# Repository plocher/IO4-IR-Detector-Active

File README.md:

# IO4-IR-Detector-Active
## License: CERN Open Hardware Licence v1.2

This project started as an AT-Tiny project loosely based on [Paisley\'s designs](http://home.cogeco.ca/~rpaisley4/PhotoDetectors.html) and 
[dustinandrews instructable](http://www.instructables.com/id/Make-an-Attiny13-based-IR-proximity-sensor-for-2/step4/Wire-it-up/).

It evolved from a discrete logic circuit into an AT-Tiny one into a quad detector based on an Arduino core for ease of programming and economy of scale - one '328 is cheaper than 4x tiny's or the original (expensive) remote control TV detectors.  The current version uses a DFRobot to avoid having to low level program the AVR chips with a \'duino bootloader.

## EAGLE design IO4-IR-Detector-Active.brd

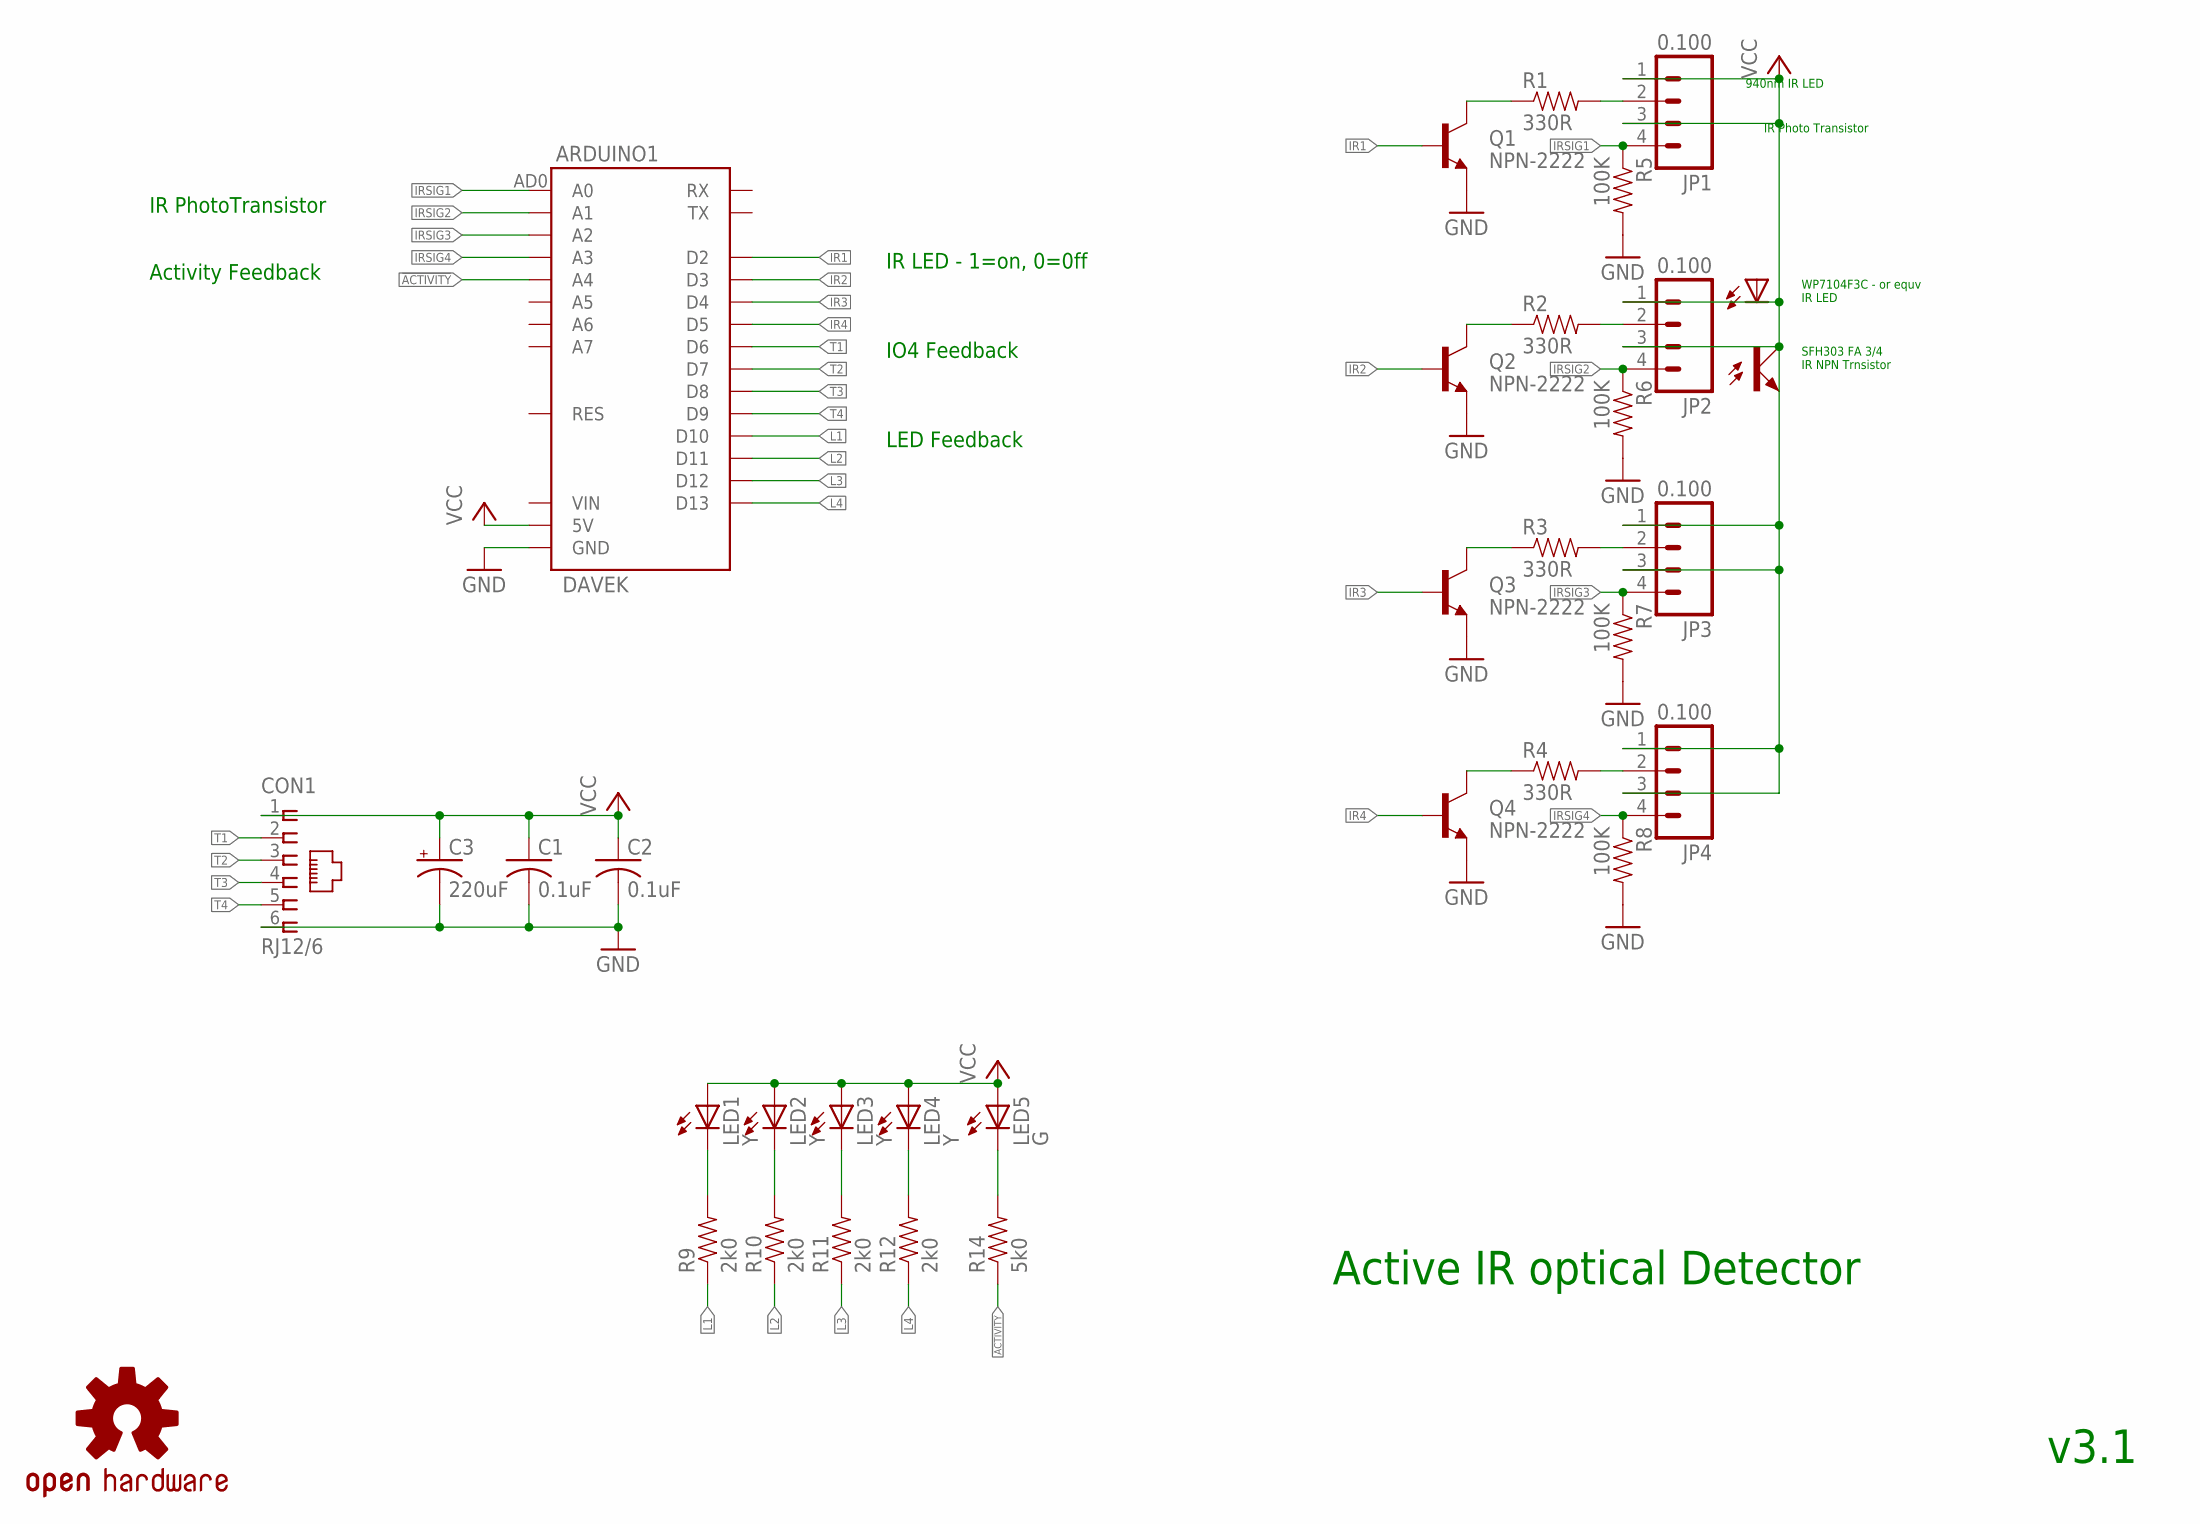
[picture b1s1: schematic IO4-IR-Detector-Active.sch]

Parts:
ARDUINO1: DAVEK; ARDUINO_PRO_MINI_DAVEK
C1, C2: 0.1uF; 0603-CAP
C3: 220uF; 0810-CAP
CON1: RJ12/6; RJ25-PANEL
JP1, JP2, JP3, JP4: 0.100; 1X04_LOCK
LED1, LED2, LED3, LED4: Y; 0603-LED
LED5: G; 0603-LED
OSH_LOGO: DOC-OSHW-LOGO-S; OSHW-LOGO-S
Q1, Q2, Q3, Q4: NPN-2222; SOT23
R1, R2, R3, R4: 330R; 0603-RES
R5, R6, R7, R8: 100K; 0603-RES
R9, R10, R11, R12: 2k0; 0603-RES
R14: 5k0; 0603-RES

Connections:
!ACTIVITY: ARDUINO1.AD4 (A4), R14.1
GND: ARDUINO1.GND@1 (GND), ARDUINO1.GND@2 (GND), ARDUINO1.GND@4 (GND), C1.2, C2.2, C3.-, CON1.6, Q1.2 (E), Q2.2 (E), Q3.2 (E), Q4.2 (E), R5.2, R6.2, R7.2, R8.2
IR1: ARDUINO1.D2, Q1.1 (B)
IR2: ARDUINO1.D3, Q2.1 (B)
IR3: ARDUINO1.D4, Q3.1 (B)
IR4: ARDUINO1.D5, Q4.1 (B)
IRDRIVE1: Q1.3 (C), R1.1
IRDRIVE2: Q2.3 (C), R2.1
IRDRIVE3: Q3.3 (C), R3.1
IRDRIVE4: Q4.3 (C), R4.1
IRSIG1: ARDUINO1.AD0 (A0), JP1.4, R5.1
IRSIG2: ARDUINO1.AD1 (A1), JP2.4, R6.1
IRSIG3: ARDUINO1.AD2 (A2), JP3.4, R7.1
IRSIG4: ARDUINO1.AD3 (A3), JP4.4, R8.1
L1: ARDUINO1.D10, R9.1
L2: ARDUINO1.D11, R10.1
L3: ARDUINO1.D12, R11.1
L4: ARDUINO1.D13, R12.1
unnamed: LED5.C, R14.2
unnamed: JP1.2, R1.2
unnamed: JP2.2, R2.2
unnamed: JP3.2, R3.2
unnamed: JP4.2, R4.2
unnamed: LED1.C, R9.2
unnamed: LED2.C, R10.2
unnamed: LED3.C, R11.2
unnamed: LED4.C, R12.2
T1: ARDUINO1.D6, CON1.2
T2: ARDUINO1.D7, CON1.3
T3: ARDUINO1.D8, CON1.4
T4: ARDUINO1.D9, CON1.5
VCC: ARDUINO1.5V, C1.1, C2.1, C3.+, CON1.1, JP1.1, JP1.3, JP2.1, JP2.3, JP3.1, JP3.3, JP4.1, JP4.3, LED1.A, LED2.A, LED3.A, LED4.A, LED5.A

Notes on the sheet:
Active IR optical Detector
v3.1
940nm IR LED
IR Photo Transistor
WP7104F3C - or equv IR LED
SFH303 FA 3/4 IR NPN Trnsistor
IR LED - 1=on, 0=0ff
IR PhotoTransistor
IO4 Feedback
LED Feedback
Activity Feedback

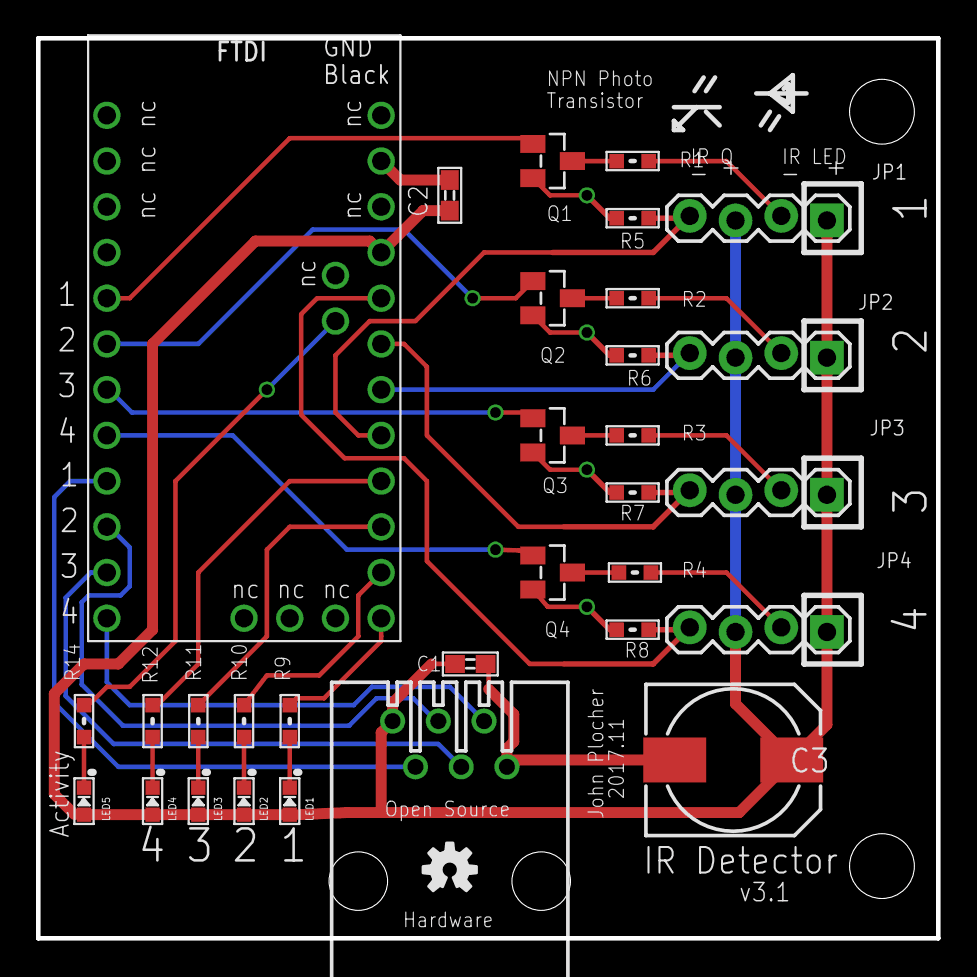
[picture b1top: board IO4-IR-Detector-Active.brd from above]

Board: 2 copper layers, 50.0 x 50.0 mm, 32 parts (0 on the bottom side), 32 nets.

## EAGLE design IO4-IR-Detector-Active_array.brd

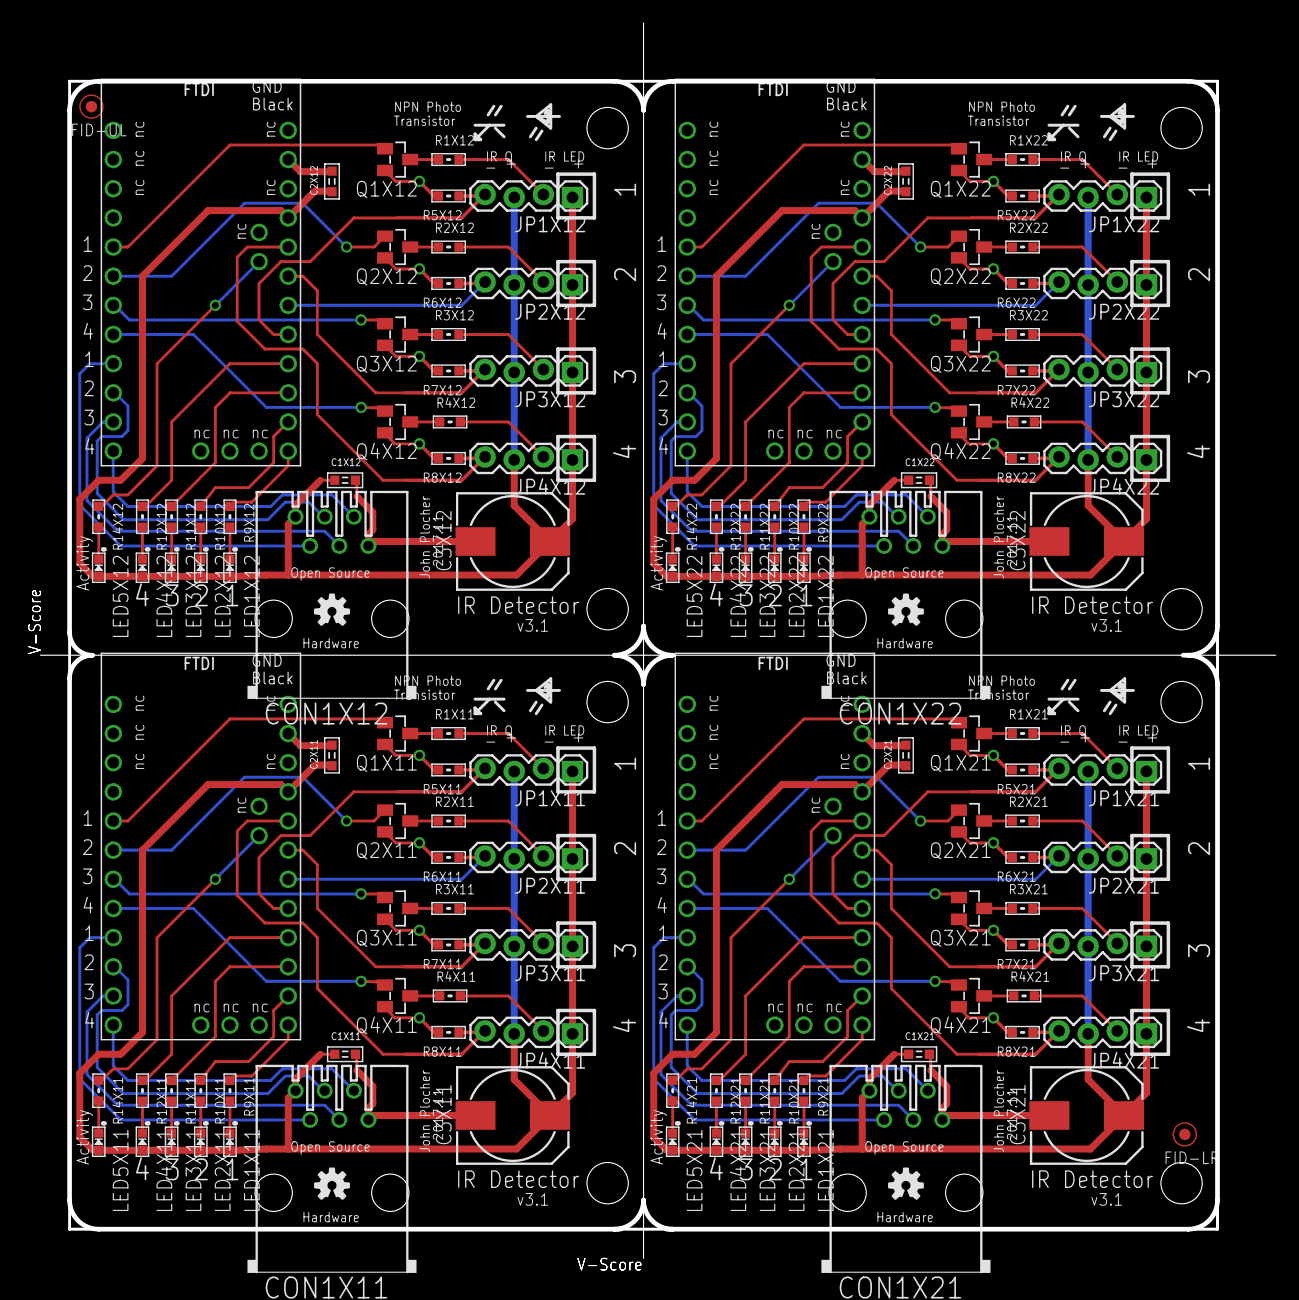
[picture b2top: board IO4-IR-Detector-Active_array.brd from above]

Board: 2 copper layers, 108.7 x 108.8 mm, 130 parts (0 on the bottom side), 128 nets.

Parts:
ARDUINO1X11, ARDUINO1X12, ARDUINO1X21, ARDUINO1X22: DAVEK; ARDUINO_PRO_MINI_DAVEK
C1X11, C1X12, C1X21, C1X22, C2X11, C2X12, C2X21, C2X22: 0.1uF; 0603-CAP
C3X11, C3X12, C3X21, C3X22: 220uF; 0810-CAP
CON1X11, CON1X12, CON1X21, CON1X22: RJ12/6; RJ25-PANEL
FID-LR: FIDUCIAL_1MM
FID-UL: FIDUCIAL_1MM
JP1X11, JP1X12, JP1X21, JP1X22, JP2X11, JP2X12, JP2X21, JP2X22, JP3X11, JP3X12, JP3X21, JP3X22, JP4X11, JP4X12, JP4X21, JP4X22: 0.100; 1X04_LOCK
LED1X11, LED1X12, LED1X21, LED1X22, LED2X11, LED2X12, LED2X21, LED2X22, LED3X11, LED3X12, LED3X21, LED3X22, LED4X11, LED4X12, LED4X21, LED4X22: Y; 0603-LED
LED5X11, LED5X12, LED5X21, LED5X22: G; 0603-LED
OSH_LOGOX11, OSH_LOGOX12, OSH_LOGOX21, OSH_LOGOX22: DOC-OSHW-LOGO-S; OSHW-LOGO-S
Q1X11, Q1X12, Q1X21, Q1X22, Q2X11, Q2X12, Q2X21, Q2X22, Q3X11, Q3X12, Q3X21, Q3X22, Q4X11, Q4X12, Q4X21, Q4X22: NPN-2222; SOT23
R1X11, R1X12, R1X21, R1X22, R2X11, R2X12, R2X21, R2X22, R3X11, R3X12, R3X21, R3X22, R4X11, R4X12, R4X21, R4X22: 330R; 0603-RES
R5X11, R5X12, R5X21, R5X22, R6X11, R6X12, R6X21, R6X22, R7X11, R7X12, R7X21, R7X22, R8X11, R8X12, R8X21, R8X22: 100K; 0603-RES
R9X11, R9X12, R9X21, R9X22, R10X11, R10X12, R10X21, R10X22, R11X11, R11X12, R11X21, R11X22, R12X11, R12X12, R12X21, R12X22: 2k0; 0603-RES
R14X11, R14X12, R14X21, R14X22: 5k0; 0603-RES

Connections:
!ACTIVITYX11: ARDUINO1X11.AD4, R14X11.1
!ACTIVITYX12: ARDUINO1X12.AD4, R14X12.1
!ACTIVITYX21: ARDUINO1X21.AD4, R14X21.1
!ACTIVITYX22: ARDUINO1X22.AD4, R14X22.1
GNDX11: ARDUINO1X11.GND@1, ARDUINO1X11.GND@2, ARDUINO1X11.GND@4, C1X11.2, C2X11.2, C3X11.-, CON1X11.6, Q1X11.2, Q2X11.2, Q3X11.2, Q4X11.2, R5X11.2, R6X11.2, R7X11.2, R8X11.2
GNDX12: ARDUINO1X12.GND@1, ARDUINO1X12.GND@2, ARDUINO1X12.GND@4, C1X12.2, C2X12.2, C3X12.-, CON1X12.6, Q1X12.2, Q2X12.2, Q3X12.2, Q4X12.2, R5X12.2, R6X12.2, R7X12.2, R8X12.2
GNDX21: ARDUINO1X21.GND@1, ARDUINO1X21.GND@2, ARDUINO1X21.GND@4, C1X21.2, C2X21.2, C3X21.-, CON1X21.6, Q1X21.2, Q2X21.2, Q3X21.2, Q4X21.2, R5X21.2, R6X21.2, R7X21.2, R8X21.2
GNDX22: ARDUINO1X22.GND@1, ARDUINO1X22.GND@2, ARDUINO1X22.GND@4, C1X22.2, C2X22.2, C3X22.-, CON1X22.6, Q1X22.2, Q2X22.2, Q3X22.2, Q4X22.2, R5X22.2, R6X22.2, R7X22.2, R8X22.2
IR1X11: ARDUINO1X11.D2, Q1X11.1
IR1X12: ARDUINO1X12.D2, Q1X12.1
IR1X21: ARDUINO1X21.D2, Q1X21.1
IR1X22: ARDUINO1X22.D2, Q1X22.1
IR2X11: ARDUINO1X11.D3, Q2X11.1
IR2X12: ARDUINO1X12.D3, Q2X12.1
IR2X21: ARDUINO1X21.D3, Q2X21.1
IR2X22: ARDUINO1X22.D3, Q2X22.1
IR3X11: ARDUINO1X11.D4, Q3X11.1
IR3X12: ARDUINO1X12.D4, Q3X12.1
IR3X21: ARDUINO1X21.D4, Q3X21.1
IR3X22: ARDUINO1X22.D4, Q3X22.1
IR4X11: ARDUINO1X11.D5, Q4X11.1
IR4X12: ARDUINO1X12.D5, Q4X12.1
IR4X21: ARDUINO1X21.D5, Q4X21.1
IR4X22: ARDUINO1X22.D5, Q4X22.1
IRDRIVE1X11: Q1X11.3, R1X11.1
IRDRIVE1X12: Q1X12.3, R1X12.1
IRDRIVE1X21: Q1X21.3, R1X21.1
IRDRIVE1X22: Q1X22.3, R1X22.1
IRDRIVE2X11: Q2X11.3, R2X11.1
IRDRIVE2X12: Q2X12.3, R2X12.1
IRDRIVE2X21: Q2X21.3, R2X21.1
IRDRIVE2X22: Q2X22.3, R2X22.1
IRDRIVE3X11: Q3X11.3, R3X11.1
IRDRIVE3X12: Q3X12.3, R3X12.1
IRDRIVE3X21: Q3X21.3, R3X21.1
IRDRIVE3X22: Q3X22.3, R3X22.1
IRDRIVE4X11: Q4X11.3, R4X11.1
IRDRIVE4X12: Q4X12.3, R4X12.1
IRDRIVE4X21: Q4X21.3, R4X21.1
IRDRIVE4X22: Q4X22.3, R4X22.1
IRSIG1X11: ARDUINO1X11.AD0, JP1X11.4, R5X11.1
IRSIG1X12: ARDUINO1X12.AD0, JP1X12.4, R5X12.1
IRSIG1X21: ARDUINO1X21.AD0, JP1X21.4, R5X21.1
IRSIG1X22: ARDUINO1X22.AD0, JP1X22.4, R5X22.1
IRSIG2X11: ARDUINO1X11.AD1, JP2X11.4, R6X11.1
IRSIG2X12: ARDUINO1X12.AD1, JP2X12.4, R6X12.1
IRSIG2X21: ARDUINO1X21.AD1, JP2X21.4, R6X21.1
IRSIG2X22: ARDUINO1X22.AD1, JP2X22.4, R6X22.1
IRSIG3X11: ARDUINO1X11.AD2, JP3X11.4, R7X11.1
IRSIG3X12: ARDUINO1X12.AD2, JP3X12.4, R7X12.1
IRSIG3X21: ARDUINO1X21.AD2, JP3X21.4, R7X21.1
IRSIG3X22: ARDUINO1X22.AD2, JP3X22.4, R7X22.1
IRSIG4X11: ARDUINO1X11.AD3, JP4X11.4, R8X11.1
IRSIG4X12: ARDUINO1X12.AD3, JP4X12.4, R8X12.1
IRSIG4X21: ARDUINO1X21.AD3, JP4X21.4, R8X21.1
IRSIG4X22: ARDUINO1X22.AD3, JP4X22.4, R8X22.1
L1X11: ARDUINO1X11.D10, R9X11.1
L1X12: ARDUINO1X12.D10, R9X12.1
L1X21: ARDUINO1X21.D10, R9X21.1
L1X22: ARDUINO1X22.D10, R9X22.1
L2X11: ARDUINO1X11.D11, R10X11.1
L2X12: ARDUINO1X12.D11, R10X12.1
L2X21: ARDUINO1X21.D11, R10X21.1
L2X22: ARDUINO1X22.D11, R10X22.1
L3X11: ARDUINO1X11.D12, R11X11.1
L3X12: ARDUINO1X12.D12, R11X12.1
L3X21: ARDUINO1X21.D12, R11X21.1
L3X22: ARDUINO1X22.D12, R11X22.1
L4X11: ARDUINO1X11.D13, R12X11.1
L4X12: ARDUINO1X12.D13, R12X12.1
L4X21: ARDUINO1X21.D13, R12X21.1
L4X22: ARDUINO1X22.D13, R12X22.1
unnamed: LED5X11.C, R14X11.2
unnamed: LED5X12.C, R14X12.2
unnamed: LED5X21.C, R14X21.2
unnamed: LED5X22.C, R14X22.2
unnamed: JP1X11.2, R1X11.2
unnamed: JP1X12.2, R1X12.2
unnamed: JP1X21.2, R1X21.2
unnamed: JP1X22.2, R1X22.2
unnamed: JP2X11.2, R2X11.2
unnamed: JP2X12.2, R2X12.2
unnamed: JP2X21.2, R2X21.2
unnamed: JP2X22.2, R2X22.2
unnamed: JP3X11.2, R3X11.2
unnamed: JP3X12.2, R3X12.2
unnamed: JP3X21.2, R3X21.2
unnamed: JP3X22.2, R3X22.2
unnamed: JP4X11.2, R4X11.2
unnamed: JP4X12.2, R4X12.2
unnamed: JP4X21.2, R4X21.2
unnamed: JP4X22.2, R4X22.2
unnamed: LED1X11.C, R9X11.2
unnamed: LED1X12.C, R9X12.2
unnamed: LED1X21.C, R9X21.2
unnamed: LED1X22.C, R9X22.2
unnamed: LED2X11.C, R10X11.2
unnamed: LED2X12.C, R10X12.2
unnamed: LED2X21.C, R10X21.2
unnamed: LED2X22.C, R10X22.2
unnamed: LED3X11.C, R11X11.2
unnamed: LED3X12.C, R11X12.2
unnamed: LED3X21.C, R11X21.2
unnamed: LED3X22.C, R11X22.2
unnamed: LED4X11.C, R12X11.2
unnamed: LED4X12.C, R12X12.2
unnamed: LED4X21.C, R12X21.2
unnamed: LED4X22.C, R12X22.2
T1X11: ARDUINO1X11.D6, CON1X11.2
T1X12: ARDUINO1X12.D6, CON1X12.2
T1X21: ARDUINO1X21.D6, CON1X21.2
T1X22: ARDUINO1X22.D6, CON1X22.2
T2X11: ARDUINO1X11.D7, CON1X11.3
T2X12: ARDUINO1X12.D7, CON1X12.3
T2X21: ARDUINO1X21.D7, CON1X21.3
T2X22: ARDUINO1X22.D7, CON1X22.3
T3X11: ARDUINO1X11.D8, CON1X11.4
T3X12: ARDUINO1X12.D8, CON1X12.4
T3X21: ARDUINO1X21.D8, CON1X21.4
T3X22: ARDUINO1X22.D8, CON1X22.4
T4X11: ARDUINO1X11.D9, CON1X11.5
T4X12: ARDUINO1X12.D9, CON1X12.5
T4X21: ARDUINO1X21.D9, CON1X21.5
T4X22: ARDUINO1X22.D9, CON1X22.5
VCCX11: ARDUINO1X11.5V, C1X11.1, C2X11.1, C3X11.+, CON1X11.1, JP1X11.1, JP1X11.3, JP2X11.1, JP2X11.3, JP3X11.1, JP3X11.3, JP4X11.1, JP4X11.3, LED1X11.A, LED2X11.A, LED3X11.A, LED4X11.A, LED5X11.A
VCCX12: ARDUINO1X12.5V, C1X12.1, C2X12.1, C3X12.+, CON1X12.1, JP1X12.1, JP1X12.3, JP2X12.1, JP2X12.3, JP3X12.1, JP3X12.3, JP4X12.1, JP4X12.3, LED1X12.A, LED2X12.A, LED3X12.A, LED4X12.A, LED5X12.A
VCCX21: ARDUINO1X21.5V, C1X21.1, C2X21.1, C3X21.+, CON1X21.1, JP1X21.1, JP1X21.3, JP2X21.1, JP2X21.3, JP3X21.1, JP3X21.3, JP4X21.1, JP4X21.3, LED1X21.A, LED2X21.A, LED3X21.A, LED4X21.A, LED5X21.A
VCCX22: ARDUINO1X22.5V, C1X22.1, C2X22.1, C3X22.+, CON1X22.1, JP1X22.1, JP1X22.3, JP2X22.1, JP2X22.3, JP3X22.1, JP3X22.3, JP4X22.1, JP4X22.3, LED1X22.A, LED2X22.A, LED3X22.A, LED4X22.A, LED5X22.A

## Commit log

2019-12-08 added graphic
2020-05-04 updated tags
2020-09-22 panelized
2020-10-05 added values for connectors
2020-10-06 normalized values
2020-12-27 make room for conveyer fingers

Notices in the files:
parts and their libraries:
SPCoast: http://freedomdefined.org/OSHW Creative Commons - Attribution - ShareAlike 3.0
